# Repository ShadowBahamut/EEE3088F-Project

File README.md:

# EEE3088F-Project
The following Repo contains the files for the EEE3088F Micromouse Project.
It is sorted into the 2 seperate subsystems that had to be developed and all files can be found under their respective subsystems.

If you see anything wrong don't hesitate to create a issues and I'll get back to you as soon as possible

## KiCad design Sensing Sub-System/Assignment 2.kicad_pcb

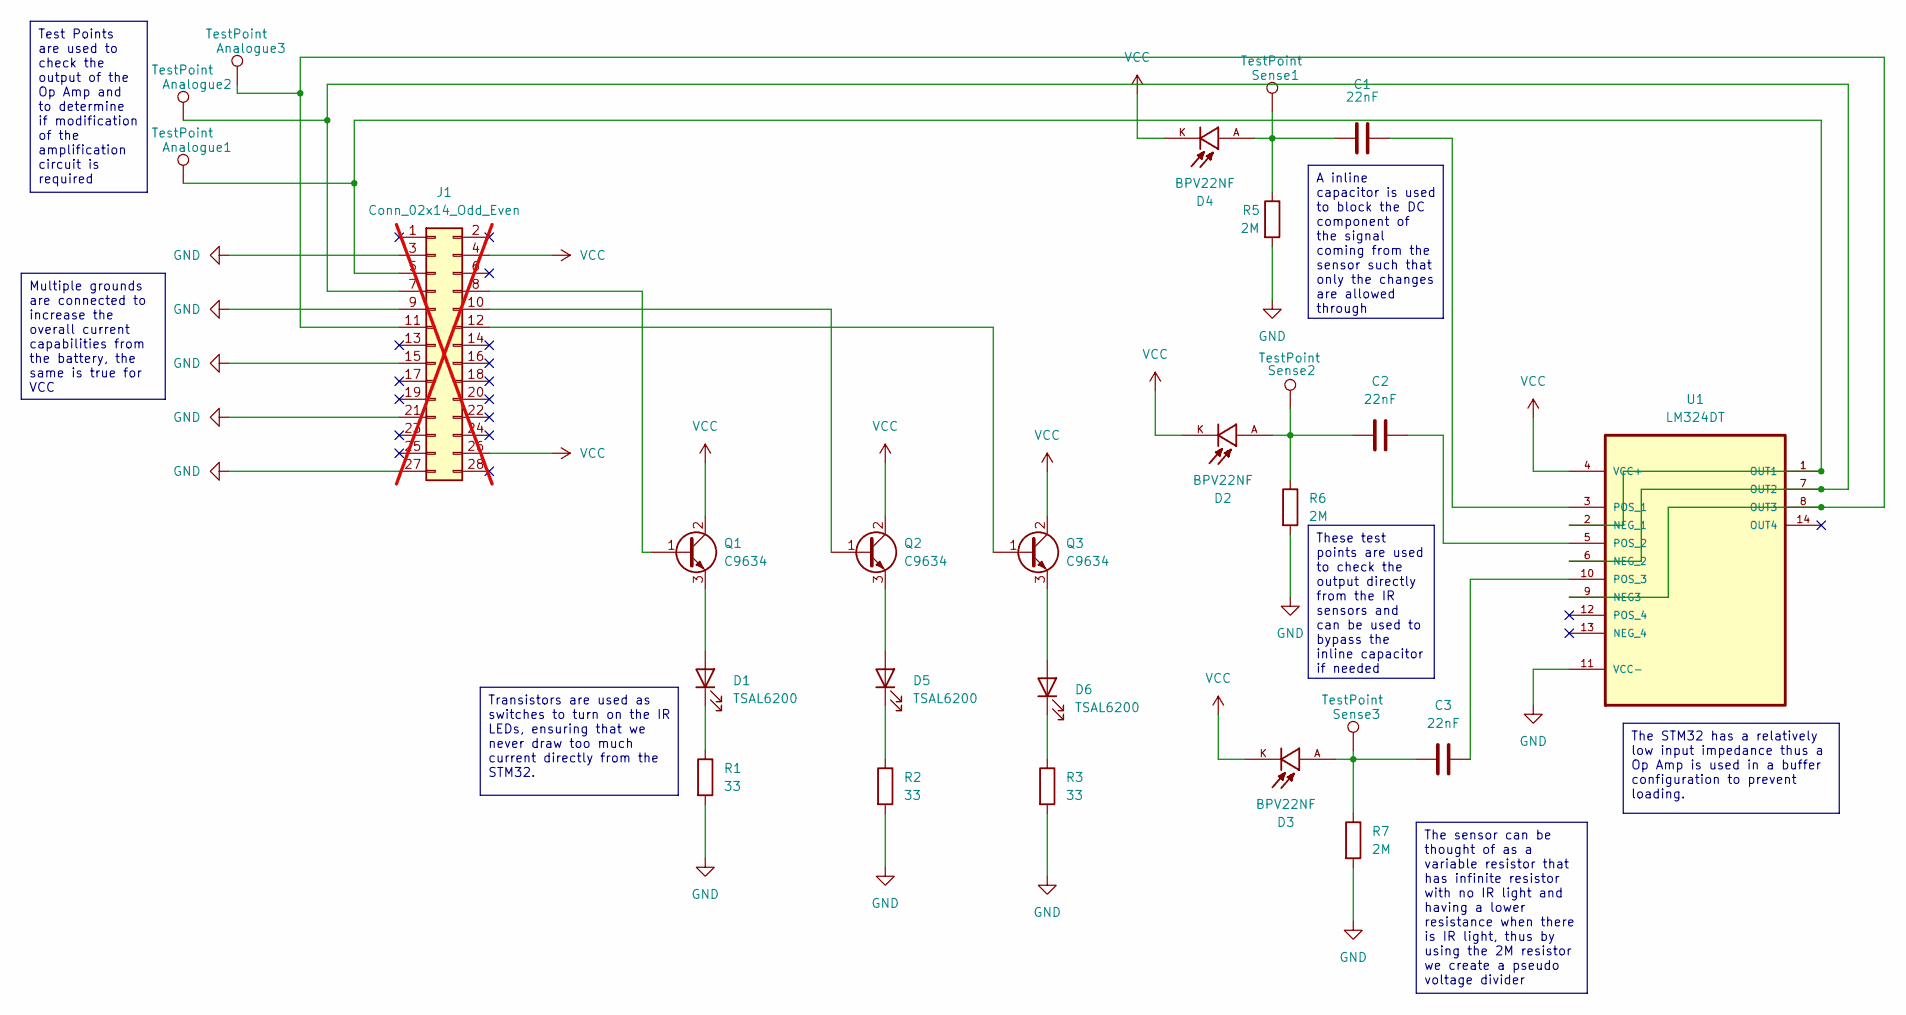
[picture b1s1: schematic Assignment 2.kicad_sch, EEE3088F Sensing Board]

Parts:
Analogue1, Analogue2, Analogue3: TestPoint; TestPoint_Pad_D2.0mm
C1, C2, C3: 22nF; C_0603_1608Metric
D1, D5, D6: TSAL6200; LED_D5.0mm_Horizontal_O6.35mm_Z15.0mm
D2, D3, D4: BPV22NF; XDCR_BPV22NF; PARTREV 1.9
J1: Conn_02x14_Odd_Even; PinHeader_2x14_P2.54mm_Vertical; not fitted
Q1, Q2, Q3: C9634; SOT-89-3
R1, R2, R3: 33; R_0603_1608Metric
R5, R6, R7: 2M; R_0603_1608Metric
Sense1, Sense2, Sense3: TestPoint; TestPoint_Pad_D2.0mm
U1: LM324DT; SOIC127P600X175-14N; MPN LM324DT

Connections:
GND: J1.3, J1.9, J1.15, J1.21, J1.27, R1.2, R2.2, R3.2, R5.2, R6.2, R7.2, U1.11 (VCC-)
unnamed: C1.1, D4.A, R5.1, Sense1.1
unnamed: C2.1, D2.A, R6.1, Sense2.1
unnamed: C3.1, D3.A, R7.1, Sense3.1
unnamed: D1.2 (A), Q1.3 (E)
unnamed: D1.1 (K), R1.1
unnamed: D5.2 (A), Q2.3 (E)
unnamed: D5.1 (K), R2.1
unnamed: D6.2 (A), Q3.3 (E)
unnamed: D6.1 (K), R3.1
unnamed: Analogue1.1, J1.5, U1.1 (OUT1), U1.2 (NEG_1)
unnamed: Analogue2.1, J1.7, U1.6 (NEG_2), U1.7 (OUT2)
unnamed: J1.8, Q1.1 (B)
unnamed: J1.10, Q2.1 (B)
unnamed: Analogue3.1, J1.11, U1.8 (OUT3), U1.9 (NEG3)
unnamed: J1.12, Q3.1 (B)
unnamed: C1.2, U1.3 (POS_1)
unnamed: C2.2, U1.5 (POS_2)
unnamed: C3.2, U1.10 (POS_3)
VCC: D2.K, D3.K, D4.K, J1.4, J1.26, Q1.2 (C), Q2.2 (C), Q3.2 (C), U1.4 (VCC+)

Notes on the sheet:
The STM32 has a relatively low input impedance thus a Op Amp is used in a buffer configuration to prevent loading.
Transistors are used as switches to turn on the IR LEDs, ensuring that we never draw too much current directly from the STM32.
Test Points are used to check the output of the Op Amp and to determine if modification of the amplification circuit is required
These test points are used to check the output directly from the IR sensors and can be used to bypass the inline capacitor if needed
The sensor can be thought of as a variable resistor that has infinite resistor with no IR light and having a lower resistance when there is IR light, thus by using the 2M resistor we create a pseudo voltage divider
Multiple grounds are connected to increase the overall current capabilities from the battery, the same is true for VCC
A inline capacitor is used to block the DC component of the signal coming from the sensor such that only the changes are allowed through

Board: 2 copper layers, 26 parts (0 on the bottom side), 20 nets, no tracks yet.

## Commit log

2024-04-21 Create tobedeleted
2024-04-21 Added KiCAD files
2024-04-21 Uploaded Gerbers
